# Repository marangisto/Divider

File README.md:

# Divider
Eurorack Modular Clock Divider

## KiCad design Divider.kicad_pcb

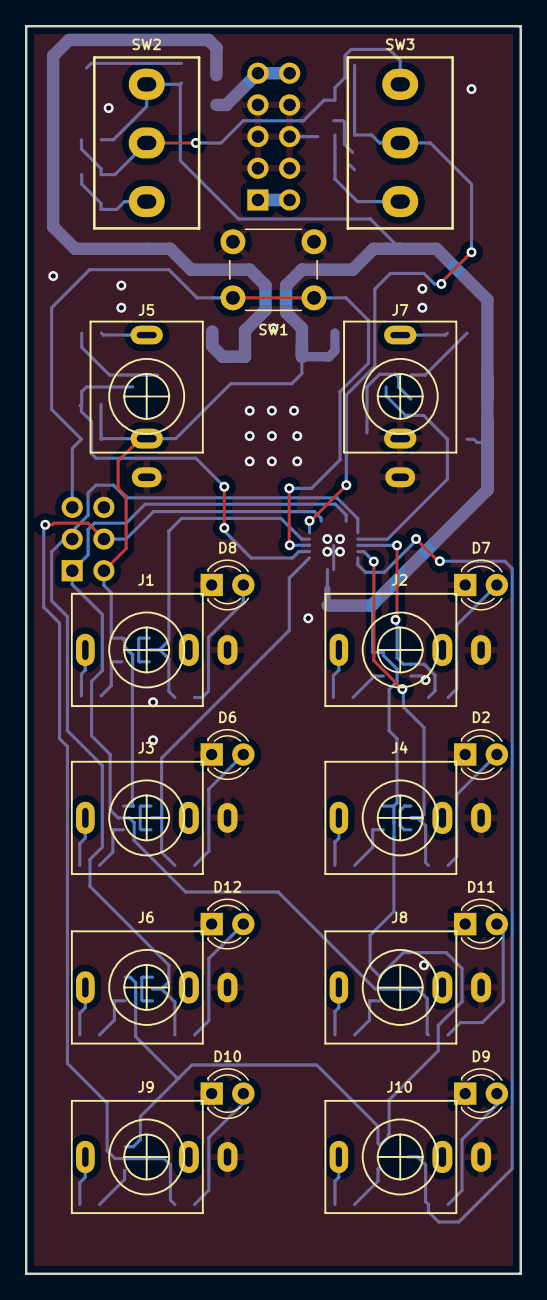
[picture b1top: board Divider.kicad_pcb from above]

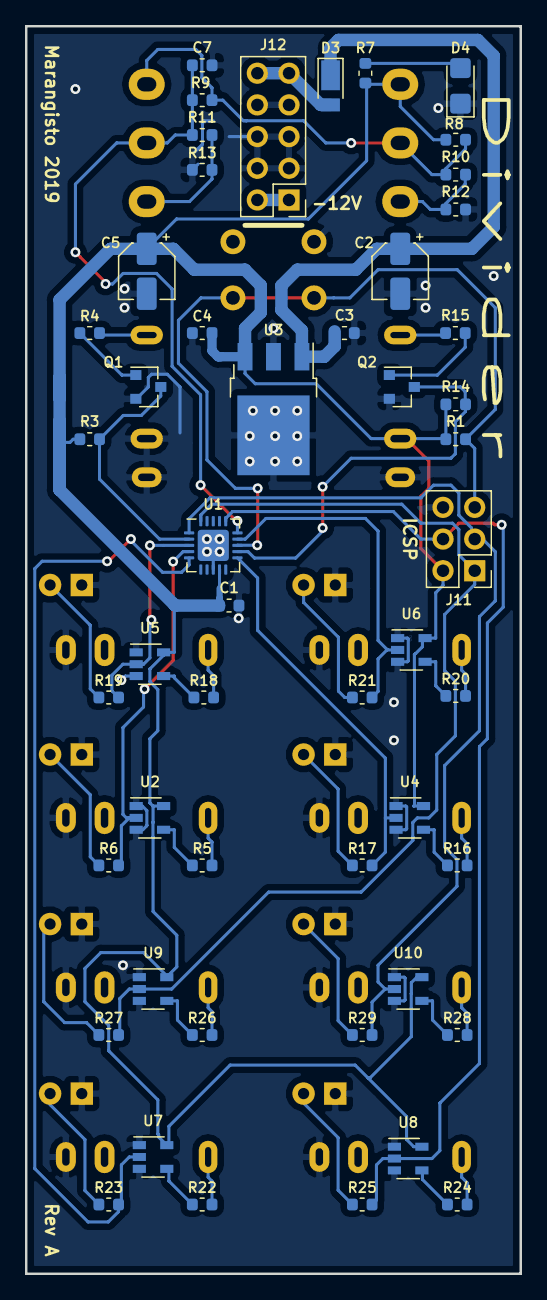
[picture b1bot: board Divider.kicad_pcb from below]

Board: 2 copper layers, 39.6 x 100.0 mm, 71 parts (50 on the bottom side), 49 nets.

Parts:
C1, C3, C4, C7: 100n; C_0603_1608Metric
C2, C5: 10u; CP_Elec_4x5.8
D2, D6, D7, D8, D9, D10, D11, D12: LED; LED_D3.0mm
D3: DFLR1400-7; D_PowerDI-123
D4: LED; LED_1206_3216Metric_Castellated
J1, J2, J3, J4, J5, J6, J7, J8, J9, J10: AudioJack2_SwitchT; PJ398SM
J11: Conn_02x03_Odd_Even; PinHeader_2x03_P2.54mm_Vertical
J12: Conn_02x05_Odd_Even; PinHeader_2x05_P2.54mm_Vertical
Q1, Q2: BC847; SOT-23
R1, R3, R14: 10k; R_0603_1608Metric
R4, R15: 100k; R_0603_1608Metric
R5, R16, R18, R20, R22, R24, R26, R28: 1k; R_0603_1608Metric
R6, R7, R17, R19, R21, R23, R25, R27, R29: 330; R_0603_1608Metric
R8: 4k7; R_0603_1608Metric
R9: 15k; R_0603_1608Metric
R10: 68k; R_0603_1608Metric
R11: 33k; R_0603_1608Metric
R12: 3k3; R_0603_1608Metric
R13: 22k; R_0603_1608Metric
SW1: SW_Push; SW_PUSH_6mm_H9.5mm
SW2, SW3: SW_SPDT_MSM; SPDT
U1: ATtiny84-20MU; QFN-20-1EP_4x4mm_P0.5mm_EP2.5x2.5mm
U2, U4, U5, U6, U7, U8, U9, U10: 74AHCT1G125; SOT-23-5
U3: L7805; TO-252-3_TabPin2

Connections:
+5V: C1.1, C4.1, C5.1, J5.TN, J11.2, R1.1, R3.1, R7.1, R8.1, R14.1, SW2.3, U1.9, U2.5, U3.3, U4.5, U5.5, U6.5, U7.5, U8.5, U9.5, U10.5
+12V: C2.1, C3.1, D3.1, U3.1
/DigitalIn/In: J7.T, R4.1
/DigitalOut/Out: J4.T, R5.1
/sheet5C2AB00C/In: J5.T, R15.1
/sheet5C2AE401/Out: J3.T, R16.1
/sheet5C2AEF1D/Out: J1.T, R20.1
/sheet5C2AEF07/Out: J2.T, R18.1
/sheet5C2AFDF5/Out: J10.T, R22.1
/sheet5C2AFE0B/Out: J9.T, R24.1
/sheet5C2AFE21/Out: J8.T, R26.1
/sheet5C2AFE37/Out: J6.T, R28.1
CLK: Q2.3, R14.2, U1.12
GND: C1.2, C2.2, C3.2, C4.2, C5.2, C7.2, D2.1, D4.1, D6.1, D7.1, D8.1, D9.1, D10.1, D11.1, D12.1, J1.S, J2.S, J3.S, J4.S, J5.S, J6.S, J7.S, J7.TN, J8.S, J9.S, J10.S, J11.6, J12.3, J12.4, J12.5, J12.6, J12.7, J12.8, Q1.2, Q2.2, R12.2, R13.2, SW1.2, U1.8, U1.21, U2.1, U2.3, U3.2, U4.1, U4.3, U5.1, U5.3, U6.1, U6.3, U7.1, U7.3, U8.1, U8.3, U9.1, U9.3, U10.1, U10.3
MISO: J11.1, R27.1, U1.20, U9.2
MOSI: J11.4, R25.1, U1.16, U8.2
unnamed: D2.2, R6.2
unnamed: D3.2, J12.9, J12.10
unnamed: D4.2, R7.2
unnamed: D6.2, R17.2
unnamed: D7.2, R19.2
unnamed: D8.2, R21.2
unnamed: D9.2, R23.2
unnamed: D10.2, R25.2
unnamed: D11.2, R27.2
unnamed: D12.2, R29.2
unnamed: J12.1, J12.2
unnamed: Q1.1, R4.2
unnamed: Q2.1, R15.2
unnamed: R5.2, U2.4
unnamed: R8.2, R9.1, R10.1, SW2.2, SW3.3
unnamed: R10.2, R12.1, SW2.1
unnamed: R11.2, R13.1, SW3.1
unnamed: R16.2, U4.4
unnamed: R18.2, U5.4
unnamed: R20.2, U6.4
unnamed: R22.2, U7.4
unnamed: R24.2, U8.4
unnamed: R26.2, U9.4
unnamed: R28.2, U10.4
OUT0: R21.1, U1.14, U6.2
OUT1: R19.1, U1.3, U5.2
OUT2: R17.1, U1.11, U4.2
OUT3: R6.1, U1.4, U2.2
OUT4: J11.3, R29.1, U1.1, U10.2
OUT7: R23.1, U1.5, U7.2
RESET: J11.5, R1.2, SW1.1, U1.13
RST: Q1.3, R3.2, U1.2
SPDTS: C7.1, R9.2, R11.1, SW3.2, U1.15

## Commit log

2018-12-31 Initial design.
2019-01-01 Initial placement.
2019-01-01 Manual power routing.
2019-01-01 Complete signal routing.
2019-01-01 Ground pours.
2019-01-01 Improved pour.
2019-01-02 Front silk-screen.
2019-01-02 Back silk-screen.
2019-01-02 Branding.
2019-01-02 Added Gerbers.
2019-01-02 Added drawings.
2019-01-02 Added some renderings.
2019-01-02 Updated pcb for Gerbers.
2019-01-02 Added BOM.
2019-01-02 Added closeup.
2019-01-03 Removed accidental slot.
2019-05-05 Moved firmware from AVR project.
